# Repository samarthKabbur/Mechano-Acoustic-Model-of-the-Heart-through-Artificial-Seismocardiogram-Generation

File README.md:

# Mechano-Acoustic-Model-of-the-Heart-through-Artificial-Seismocardiogram-Generation

URF Project Development Proposal for a Mechano Acoustic Model of the Heart through Artificial Seismocardiogram Generation and Cardiac Tissue Modeling
PI: Dr. Nanshu Lu, Mentor: Sarnab Bhattacarya, Researcher: Samarth Kabbur, University of Texas at Austin
Background and Statement of Objectives
1 			2			3		

Figure 1: Assorted imagery. 1. Heart with muscle damage and blocked artery. 2. SCG data collection flowchart. 3. Proposed artificial seismocardiogram generation system.
“Intelligence will transform our ability to monitor and detect heart disease,” says Dr. Peter Libby, a renowned cardiologist at Harvard-affiliated Brigham and Women's Hospital.1 His words encapsulate the ever-increasing importance of leveraging cutting-edge technologies to address one of the most prevalent and impactful health concerns affecting the public today – cardiac complications (Fig 1.1). 
At the forefront of cardiac monitoring is seismocardiography, or SCG, which allows us to measure the mechanical motion of the heart. SCG has shown remarkable promise in its utility, holding the potential to revolutionize the early detection and prediction of atrial fibrillation6, CAD7, and heart failure6,7, potentially years before they manifest clinically (Fig 1.2). While the promise of SCG is undeniable, the development of sensors capable of accurately measuring SCG and deriving meaningful physical characteristics of the heart from its signals has been hindered by challenges. Progress has been slow, and the cost of development has been prohibitive.2 In response to these limitations I aim to create a device that advances upon the capabilities of existing artificial SCG waveform generators.This device will have the ability to artificially generate a wide range of waveforms, enabling researchers to rigorously test their SCG sensors by placing them on top of artificial tissue. By doing so, we will establish an anatomically accurate mechano-acoustic model of the heart, enabling the development and testing of non-invasive devices under various simulated heart conditions (Fig 1.3). The implications of such a device are profound, as it can be employed broadly in research clinics and commercial testing, provided it receives the necessary approvals.
While existing SCG Generator Phantoms have demonstrated the ability to replicate SCG waveforms with up to 90% accuracy, there remain several unexplored avenues.3 This research seeks to answer important questions regarding the use of alternative transduction methods, such as piezoelectric, for SCG generation. Additionally, by introducing configurable noise and artifact simulation into the system, this study aims to enhance the utility of artificial SCG signal generation for algorithm testing.
The significance of this study will be underscored if the developed device consistently and accurately reproduces SCG waveforms recorded by gold standard SCG sensors in real human subjects. Furthermore, the incorporation of artificial tissue layers into the waveform generation process holds the potential to contribute to the creation of more realistic SCG waveforms, advancing the state of the art in this field.This research is expected to be of particular interest to seismocardiogram researchers and those involved in SCG sensor development, as it promises to accelerate the testing phase of their projects. Many within our laboratory share these research interests.
In conclusion, the objectives of this study are twofold: the primary objective is to assess if the inclusion of artificial tissue composed of PDMS and other biopolymers enhances the accuracy of artificial SCG waveforms, while the secondary objective seeks to explore the procedural combination of noise artifacts with SCG waveforms.  It addresses critical questions, introduces innovative approaches, and holds the promise of improving the reliability and accuracy of SCG sensor technology.
Proposed Research Plan
    1			2	                  3			   4

Figure 2: Prototype results of a speaker based SCG transduction/generation platform. 1. The 10.7cm x 10.7cm base plate and ADXL355 accelerometer 2. The hexagonal cross-structure and sandwich. 3. Side profile reveals the Visaton EX60-S electrodynamic exciter, printed support base, bottom cushion, and the top placement of direct SCG measurement 4. rPi 3B computational structure for interface with the exciter and accelerometer. The rPi hat is developed by Nikbakht et.al.
2.1 Build and validate a speaker based SCG transduction platform that allows for the vibrational playback of Heartsound.wav waveforms.
Under the guidance of my mentor and previous work on a SCG Generator Phantom (hardware and software) by Nikbakht et.al3 I have developed a mechano-acoustic foundation for the artificial generation of SCG waveforms, a critical component of our research methodology (Fig 2). This system has been structured to facilitate validation through external sensor measurements. The core of this setup features a carefully designed base plate characterized by dimensions and curvature tailored to minimize internal echoes (Fig 2.1). Positioned atop this base plate is an accelerometer, responsible for recording the SCG waveform (Fig 2.1). To bolster mechanical coupling and optimize vibration transmission, a hexagonal cross structure is sandwiched within (Fig 2.2). The uppermost layer comprises a thin, rigid printed plastic roof plate, serving as the platform for the placement of the external SCG measurement device (Fig 2.3). Connecting these elements is a Raspberry Pi housing Python code that not only transmits the SCG waveform for playback but also collects internal vibration data from the accelerometer (Fig 2.4).
This endeavor benefits from the existence of more advanced software, as seen in the work by Nikbakht et.al. This software encompasses a comprehensive suite of features, including a feedback transfer function for waveform calibration against noise, error handling mechanisms, terminal-based inputs for precise control over playback, and it performs well on my mechanical model. In my research, I intend to draw inspiration from and further develop this existing codebase to refine and optimize my own system for SCG signal generation and validation.
	2.2 Build and study the effect of anatomically correct cardiac tissue layers composed of eco-polydimethylsiloxane and other bio-polymers on the generation of accurate artificial seismocardiogram waveforms.
SCG sensors do not sit directly on top of the heart, rather they read signals that need to travel through many layers of bone and tissue, including the myocardium, peritoneum, sternum, etc.2 Using our available eco-PDMS and other biopolymers as necessary, I will create layers of variable thickness, density, and composition to create a low-level structure mimicking the anatomical layers of the heart. The layers will rest on the top surface of the existing SCG Generator. Experimental testing will determine if the biostructure allows for a generation of a more accurate SCG signal, compared to a barebones platform. The testing will include varying the mechanical coupling between layers, changing the weight of the sensor itself, and varying tissue density all as independent variables.
	2.3 Create an algorithm that can incorporate noise artifacts (walking, running, stomach palpitations, small impulse) into a clean SCG signal.
Available SCG databases are limited, and sometimes a researcher may want to test their sensors on a unique signal that isn’t available to us. For example, the topic of research may deal with creating an e-tattoo that can detect SCG features while the patient is walking, running, etc. Citation no. 2 also describes this problem as a gap in existing literature. I will create a novel program that can combine noise artifacts generated by walking, running, hiking, swimming, etc. with a ‘clean’ SCG signal, in order to simulate a ‘dirty’ signal. Such a signal would then be played in the SCG Generator for testing purposes, allowing the researcher to test their device on a large variety of signals, all on a small in-house machine, allowing them to minimize expensive human trials.
Project Schedule and Milestones
Task
Subtask
Y1
Q1
Q2
Q3
Q4

1
Optimize and groove mechanical structure 

Mitigate external noise

2
Methodize variable density PDMS production

Manufacture tissue layers

Validate signal accuracy

3
Accumulate noisy and clean datasets

Procedural generation of noisy signal

Validate signal accuracy to ground truth

Review of Literature
A seminal external study that significantly informs the present research is the work titled "A Synthetic Seismocardiogram and Electrocardiogram Generator Phantom," authored by Mohammad Nikbakht et. al. This study introduced a portable and innovative system designed to synthetically generate SCG and electrocardiogram (ECG) signals. The researchers developed a Raspberry Pi-based system capable of replicating input SCG and ECG waveforms as physical acceleration and voltage outputs. For SCG generation, an off-the-shelf exciter speaker was employed as a mechanical transducer, and its transfer function was meticulously calibrated to ensure accurate replication of SCG waveforms. The system's performance was rigorously validated using human SCG and ECG data, achieving a remarkable >90% correlation between input and output signals in both time and frequency domains. Importantly, amplitude errors were maintained within clinically acceptable ranges, allowing the system to produce realistic waveforms with amplitudes corresponding to critical cardiac features. This innovation enables safe data collection in environments unsafe for human participants and provides a valuable source of ground truth signals.
While the aforementioned study represents a significant advancement in SCG signal generation, there remain opportunities for further development and improvement. First, expanding the validation process to encompass more diverse SCG morphologies, as well as various cardiac conditions, will enhance the applicability and reliability of the synthetic signal generator. The addition of noise artifacts associated with walking, running, and other forms of human mobility to the input waveform can help synthesize the effect of real world continuous processes on the heart. Finally, the proposed research seeks to build upon this foundation by creating a device that not only generates SCG signals but also incorporates artificial tissue layers to model the complex physiological nuances of the human body.
Budget
Raspberry Pi 4b+ KIT: Faster processor unlocks real time SCG processing and computationally intensive Python packages: $186
PDMS and Crosslinker: Biopolymer to simulate tissue layers: $175
Visaton 60s Electrodynamic Actuator x2: Generates the main SCG signal: $160
PAD Ex 60s x4: $120 x2: Adheres generator to surface, minimizes noise: $20
Piezoelectric Actuator: To study other methods of SCG generation: $12
Foam Padding: To pad external connections to minimize noise and internal vibration: $5
Polylactic Acid Filament: 3D printer material for foundation fabrication: $19
Ninjaflex Polyurethane Filament: 3D printer material for flexible plastics $28
Florida Biomedical Society 2024 Conference. (Coronado Springs, Florida, Feb 8-11, 8:30-10pm daily session time). The FBSS contains 48 hours of education sessions on topics relating to biomechanics. Researcher has identified these learning opportunities as valuable for the progress of his project, and has identified attending individuals, companies, and products highly relevant to this research and my career goals: $189 Registration Fee + $144 Hotel Fee. The researcher agrees to cover all extra conference related fees to guarantee attendance. (https://www.cmia.org/events/florida-biomedical-society-2024-symposium/)
Total: $938
The materials in the itemized budget are essential to the design and production of the proposal and validation study. While basic lab materials and electronic elements are available through courtesy of the PI, URF funding will expedite my research progress. It will also allow for stronger validation testing, robust manufacturing of the model, and quality materials.
References Cited
1.	Can a smart watch diagnose a heart attack? Harvard Health https://www.health.harvard.edu/heart-health/can-a-smart-watch-diagnose-a-heart-attack.
2.	Taebi, A., Solar, B. E., Bomar, A. J., Sandler, R. H. & Mansy, H. A. Recent Advances in Seismocardiography. Vibration 2, 64–86 (2019). doi: 10.3390/vibration2010005.
3.	A Synthetic Seismocardiogram and Electrocardiogram Generator Phantom. doi:10.1109/SENSORS52175.2022.9967101 
4.	Blocked Artery https://www.flickr.com/photos/nihgov/33328945325.
5.	Heart beat detection algorithm flowchart. https://www.researchgate.net/figure/Heart-beat-detection-algorithm-flowchart_fig3_33661771
6. M. Pankaala et al., “Detection of atrial fibrillation with seismocardiography,” doi: 10.1109/EMBC.2016.7591695.
7. I. Korzeniowska‐Kubacka, “Usefulness of Seismocardiography,” doi: 10.1111/j.1542-474X.2005.00547.x.

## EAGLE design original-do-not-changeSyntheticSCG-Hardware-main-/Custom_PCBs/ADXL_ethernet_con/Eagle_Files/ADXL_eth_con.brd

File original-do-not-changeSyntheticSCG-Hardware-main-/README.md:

# Synthetic ECG SCG Generator Hardware

The seismocardiogram (SCG) is a measure of chest wall vibrations resulting from the heartbeat. The SCG is typically
recorded using a low-noise accelerometer placed on the mid-sternum and contains features related to cardiovascular
activity such as aortic valve opening (AO) and aortic closing (AC). These features can support assessment of cardiovascular health and have been used in conjunction with other physiological signals to monitor key health parameters such as blood volume status and intracardiac filling pressures.

Electrocardiogram (ECG) signal reflects the electrical activity of the heart observed from the strategic points of the human body and represented by quasi-periodic voltage signal.
<!-- 
These signals fiducial points correspond to characteristic events in the cardiac cycle. For the SCG, the labels correspond to the physiological event they are believed to represent: MC, mitral valve closure; IVC, isovolumetric contraction; AO, aortic valve opening; RE, rapid ejection; AC, aortic valve closure; MO, mitral valve open- ing; and RF, rapid filling. -->

<!-- However, SCG signals are small signal, and they can get distorted easily by motion artifacts. Therefore exploring denoising methods is of great importance for SCG signals. Clearing out the noise enables extraction of physiologically relevant information from SCG. To study denoising methods, we need to collect SCG signals in noisy environments, but it is unsafe to use human subjects for such data collection in some high motion environments (medical transport helicopters). To address this, here we designed a phantom that can generate SCG and ECG signals synthetically. This enables us to collect data in those noisy environmnets without human subject involvement.
 -->
In this work, we introduce a portable USB-C powered Raspberry Pi-based system that can replicate any SCG and ECG signal inputs with minimal error in forms of acceleration and voltage. The SCG signals are generated using an off the shelf exciter speaker, and the ECG signals are generated using a voltage amplifier through 3 conductive pads. The generated signals can be recorded using the same wearable devices that are used to measure human SCG and ECG signals. Thus, this system can be used as a safer, more convenient alternative to human participants in high external vibration environments for testing and validating
classification/regression tasks and noise reduction algorithms.

## The Hardware 

he system proposed in this work consists of an actuator unit and a processing unit. The actuator unit, which generates SCG and ECG signals. 

<!--  -->

The system designed here offers two user-controlled modes of operation: (1) calibration, which re-estimates the transfer function of the exciter speaker with the added load on the platform (wearable sensors) , and (2) signal generation, which generates the ECG and SCG sequences.

A block diagram of the system operation:

### Commands

1) Calibration mode: Calibrate the system (in a new environment):

calculate the transfer function of the actuator using a sine sweep and use it to calibrate the SCG beats to be ready for generation
 
```console
python3 SCG_Generator.py tf_estimate desktop
python3 SCG_Generator.py calibrate seq_synth desktop (or any file name [without .pkl])
```
<!-- 
 -->

2) Generation mode: Generate SCG waveforms:

generate SCG and ECG signals using the calibrated beats stored in the previous step

```console
python3 SCG_Generator.py generate seq_synth_calibrated desktop (or any file name you stored the calibrated signals [without .pkl])
```

<!--  -->

## Use

Depending on the type of the connection to the RPi, there are 2 options:
1) If a display is connected to the RPi (or have X11 forwarding enabled), the plots will be shown in separate windows. Use this command (this mode is default):
```console
python3 SCG_generate.py generate signal_sample_calibrated desktop
```
2) If communication is through a terminal only, the plots will be plotted in the terminal (lower quality). Use this command:
```console
python3 SCG_generate.py generate signal_sample_calibrated terminal
```
## Output Recording Samples

A sample of the generator-output SCG and ECG compared to the ECG and SCG inputs:

Bland-Altman plots of error between the measured generator-output and the real human signal input based on the amplitude of the most prominent
feature of the beats after heartbeat segmentation for (a) SCG, and (b) ECG signals. 

<!-- Zoomed in:

 -->

## Reference

Please cite this paper:

M. Nikbakht, D. J. Lin, A. H. Gazi, and O. T. Inan, “A synthetic
seismocardiogram and electrocardiogram generator phantom,” in 2022
IEEE Sensors, in press.

BibTeX format: 

@inproceedings{nikbakht2022synthetic,
title={A Synthetic Seismocardiogram and Electrocardiogram Generator Phantom},
author={Nikbakht, Mohammad, and Lin, David J., and Gazi, Asim H., and Inan, Omer T.},
note={in press},
booktitle={2022 IEEE Sensors},
% pages={Accepted},
% year={2022},
% organization={IEEE}
}

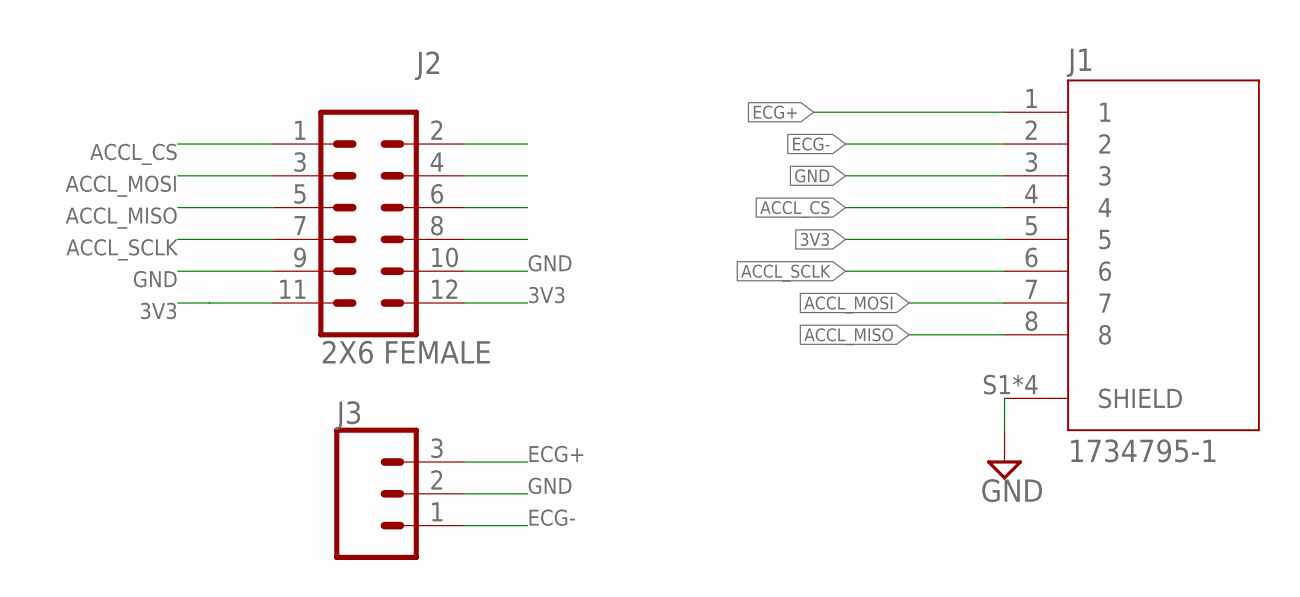
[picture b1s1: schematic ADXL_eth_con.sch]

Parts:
J1: 1734795-1; TE_1734795-1
J2: 2X6 FEMALE; 2X6
J3: CONN_03; 1X03

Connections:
3V3: J1.5, J2.11, J2.12
ACCL_CS: J1.4, J2.1
ACCL_MISO: J1.8, J2.5
ACCL_MOSI: J1.7, J2.3
ACCL_SCLK: J1.6, J2.7
ECG+: J1.1, J3.3
ECG-: J1.2, J3.1
GND: J1.3, J1.S1 (SHIELD), J1.S2 (SHIELD), J1.S3 (SHIELD), J1.S4 (SHIELD), J2.9, J2.10, J3.2

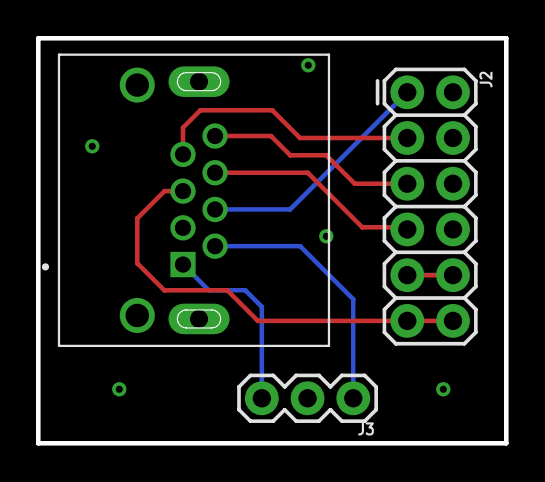
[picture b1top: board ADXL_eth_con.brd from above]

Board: 2 copper layers, 26.0 x 22.5 mm, 3 parts (0 on the bottom side), 8 nets.

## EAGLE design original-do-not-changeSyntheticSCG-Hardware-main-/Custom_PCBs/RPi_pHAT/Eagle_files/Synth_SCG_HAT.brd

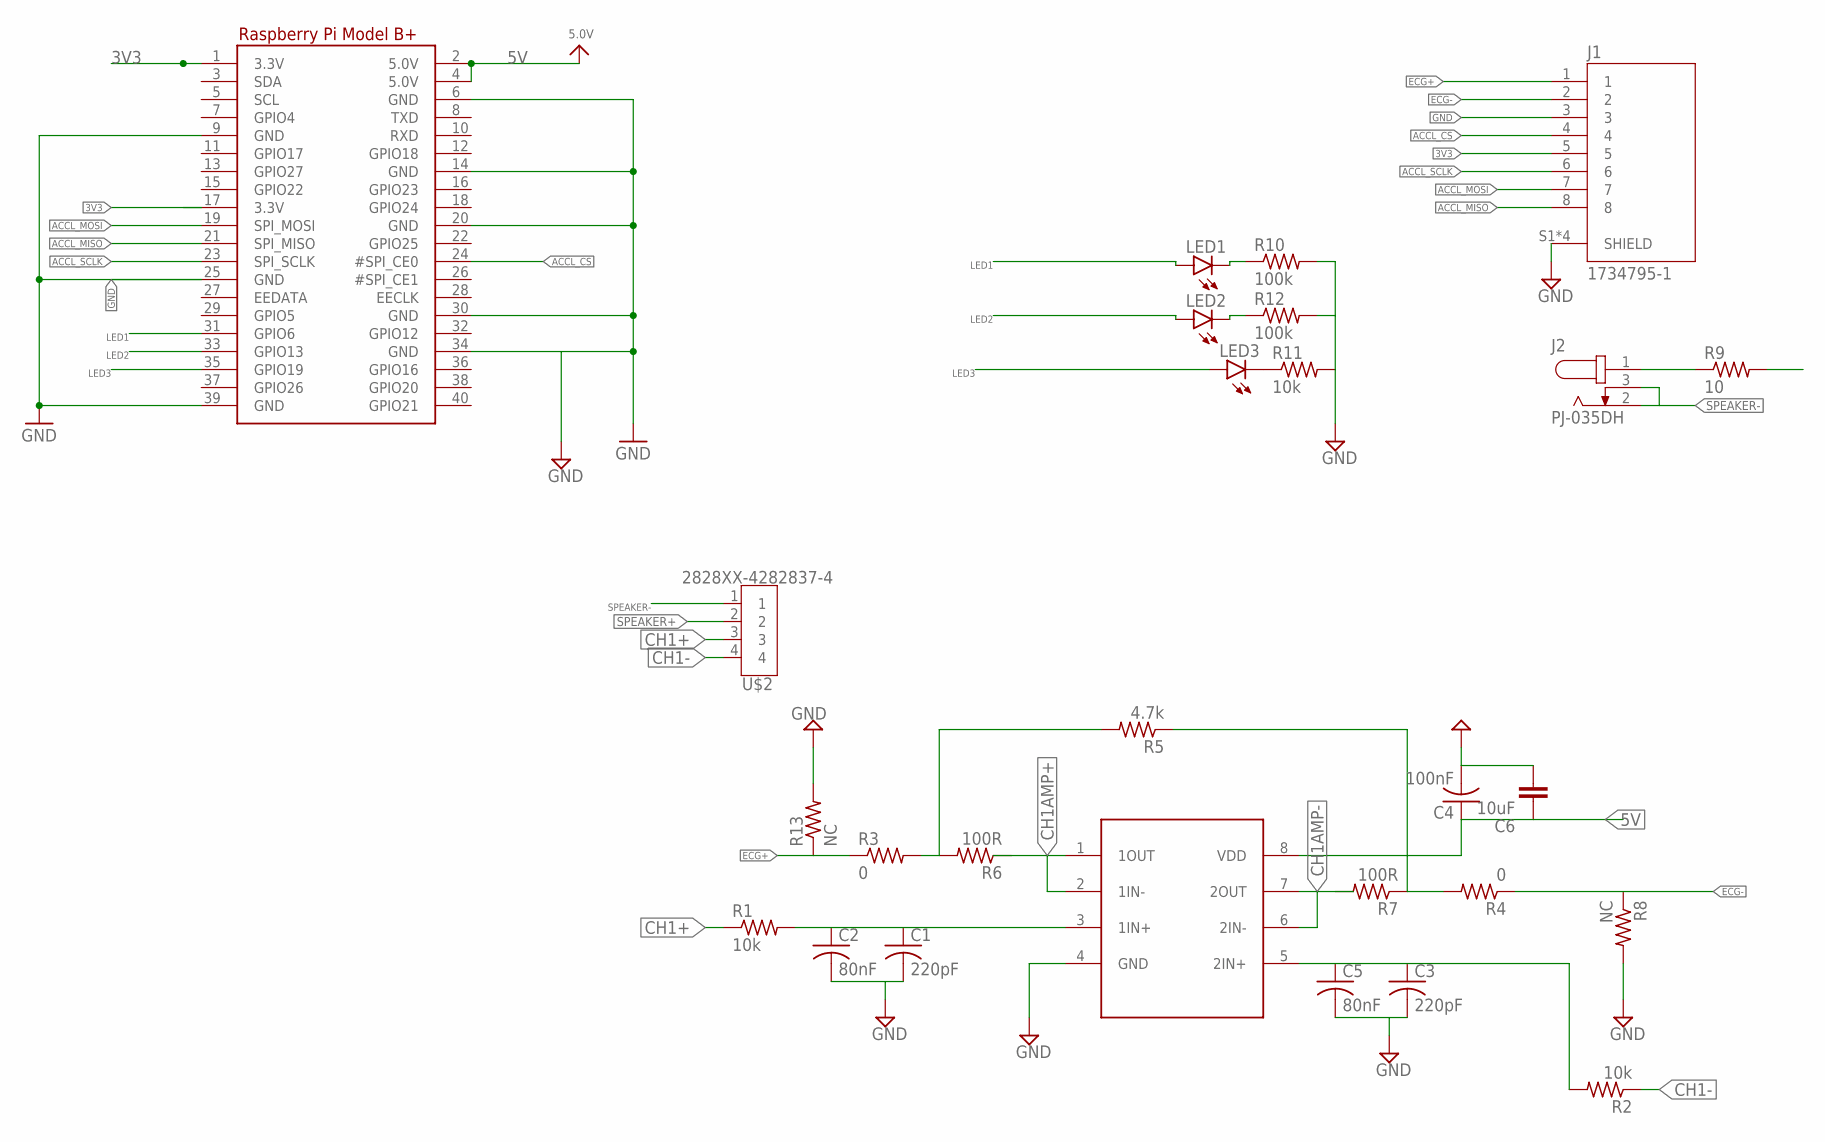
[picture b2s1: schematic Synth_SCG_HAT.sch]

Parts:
C1, C3: 220pF; CAPC3216X135
C2, C5: 80nF; CAPC2012X110
C4: 100nF; CAPC1608X85
C6: 10uF; CAPM3216X180
J1: 1734795-1; TE_1734795-1
J2: PJ-035DH; CUI_PJ-035DH
LED1, LED2, LED3: LEDCHIPLED_1206; CHIPLED_1206
R1, R2, R11: 10k; R0603
R3, R4: 0; R0603
R5: 4.7k; R0603
R6, R7: 100R; R0603
R8, R13: NC; R0603
R9: 10; R0603
R10, R12: 100k; R0603
RPI1: RASPBERRYPI_BPLUS_BONNETNODIM; PI_BONNET_NODIM
U$1: TLV4112; DIP794W45P254L959H508Q8
U$2: 2828XX-4282837-4; TERMBLK_508-4N

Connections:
3.3V@1: RPI1.17 (3.3V)
3V3: J1.5, RPI1.1 (3.3V)
5V: C4.1, C6.1, RPI1.2 (5.0V), RPI1.4 (5.0V), U$1.8 (VDD)
ACCL_CS: J1.4, RPI1.24 (#SPI_CE0)
ACCL_MISO: J1.8, RPI1.21 (SPI_MISO)
ACCL_MOSI: J1.7, RPI1.19 (SPI_MOSI)
ACCL_SCLK: J1.6, RPI1.23 (SPI_SCLK)
CH1+: R1.1, U$2.3
CH1-: R2.1, U$2.4
CH1AMP+: R6.1, U$1.1 (1OUT), U$1.2 (1IN-)
CH1AMP-: R7.2, U$1.6 (2IN-), U$1.7 (2OUT)
ECG+: J1.1, R3.1, R13.1
ECG-: J1.2, R4.1, R8.1
GND: C1.2, C2.2, C3.2, C4.2, C5.2, C6.2, J1.3, J1.S1 (SHIELD), J1.S2 (SHIELD), J1.S3 (SHIELD), J1.S4 (SHIELD), R8.2, R10.2, R11.2, R12.2, R13.2, RPI1.6 (GND), RPI1.9 (GND), RPI1.14 (GND), RPI1.20 (GND), RPI1.25 (GND), RPI1.30 (GND), RPI1.34 (GND), RPI1.39 (GND), U$1.4 (GND)
LED1: LED1.A, RPI1.31 (GPIO6)
LED2: LED2.A, RPI1.33 (GPIO13)
LED3: LED3.A, RPI1.35 (GPIO19)
unnamed: C1.1, C2.1, R1.2, U$1.3 (1IN+)
unnamed: R3.2, R5.2, R6.2
unnamed: C3.1, C5.1, R2.2, U$1.5 (2IN+)
unnamed: J2.1, R9.1
unnamed: R4.2, R5.1, R7.1
unnamed: LED3.C, R11.1
unnamed: LED2.C, R12.1
unnamed: LED1.C, R10.1
SPEAKER+: R9.2, U$2.2
SPEAKER-: J2.2, J2.3, U$2.1

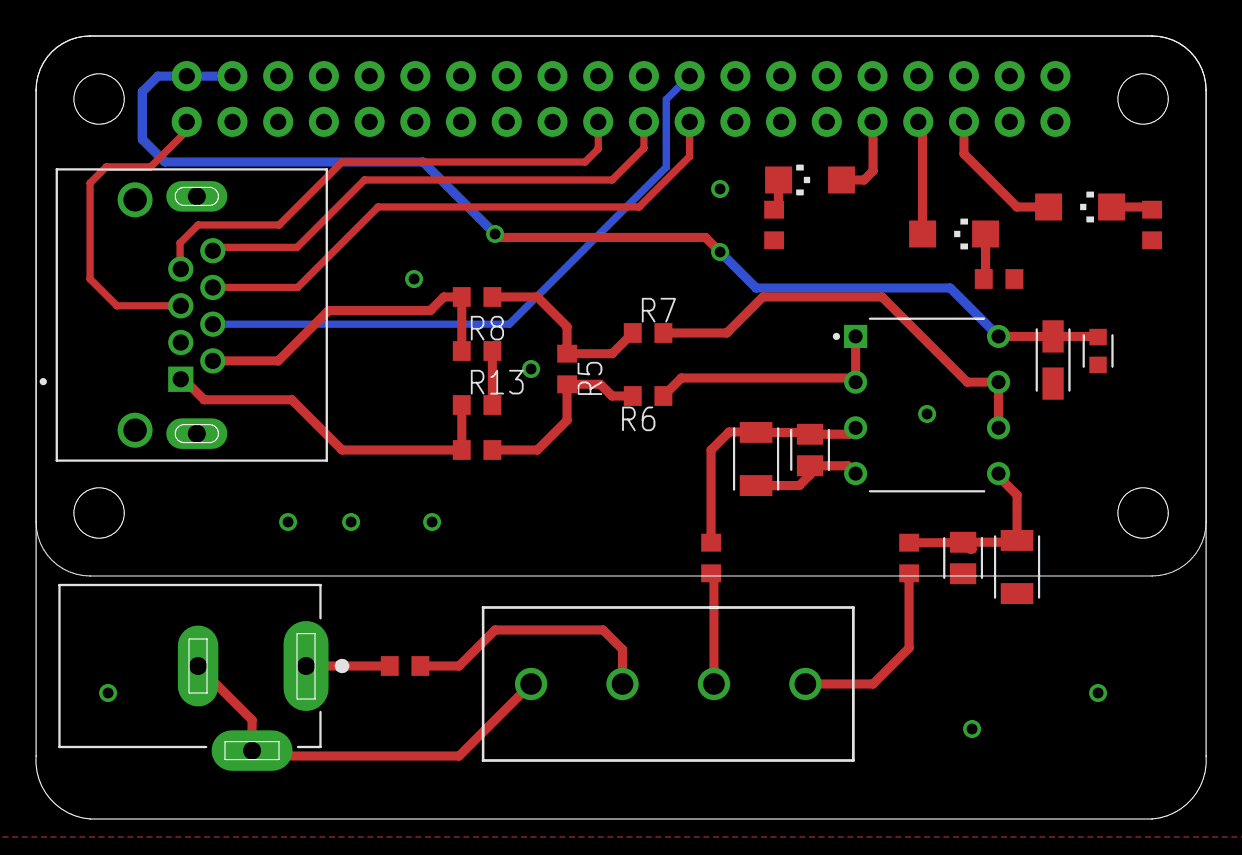
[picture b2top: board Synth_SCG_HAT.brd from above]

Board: 2 copper layers, 65.0 x 43.5 mm, 27 parts (0 on the bottom side), 26 nets.

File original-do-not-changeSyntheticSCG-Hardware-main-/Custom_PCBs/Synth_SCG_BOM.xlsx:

Part | Value | Device | Package | DigiKey Part Number
C1 | 220pF | C-US_CHIP-1206(3216-METRIC) | CAPC3216X135
C2 | 80nF | C-US_CHIP-0805(2012-METRIC) | CAPC2012X110
C3 | 220pF | C-US_CHIP-1206(3216-METRIC) | CAPC3216X135
C4 | 100nF | C-US_CHIP-0603(1608-METRIC) | CAPC1608X85
C5 | 80nF | C-US_CHIP-0805(2012-METRIC) | CAPC2012X110
C6 | 10uF | C_TANTALUM-1206(3216-METRIC) | CAPM3216X180
J1 | 1734795-1 | 1734795-1 | TE_1734795-1 | A121573-ND
J2 | PJ-035DH | PJ-035DH | CUI_PJ-035DH | CP-017DH-ND
LED1 |  | LEDCHIPLED_1206 | CHIPLED_1206
LED2 |  | LEDCHIPLED_1206 | CHIPLED_1206
LED3 |  | LEDCHIPLED_1206 | CHIPLED_1206
R1 | 10k | R-US_R0603 | R0603
R2 | 10k | R-US_R0603 | R0603
R3 | 0 | R-US_R0603 | R0603
R4 | 0 | R-US_R0603 | R0603
R5 | 4.7k | R-US_R0603 | R0603
R6 | 100R | R-US_R0603 | R0603
R7 | 100R | R-US_R0603 | R0603
R8 | NC | R-US_R0603 | R0603
R9 | 10 | R-US_R0603 | R0603
R10 | 100k | R-US_R0603 | R0603
R11 | 10k | R-US_R0603 | R0603
R12 | 100k | R-US_R0603 | R0603
R13 | NC | R-US_R0603 | R0603
RPI1 | RASPBERRYPI_BPLUS_BONNETNODIM | I2S 3W STEREO SPEAKER AMP BONNET | I2S 3W STEREO SPEAKER AMP BONNET | 1528-1819-ND
U$1 | TLV4112 | TLV4112 | DIP794W45P254L959H508Q8 | 296-10719-5-ND
U$2 | 2828XX-4282837-4 | 2828XX-4282837-4 | TERMBLK_508-4N | 281-1437-ND
 | Extra parts (digikey): |  | count
 | 2x20 Socket Riser Header for Rpi | 1528-2831-ND | 2
 | RPI female header | 1528-1785-ND | 2
 | RPi connector | 1568-1675-ND | 2
 | RPi stacking header | 1528-1385-ND
 | 12 Position Header Connector 0.100" (2.54mm) Through Hole, Right Angle | S5559-ND | 2
 | DC plug 3.5 | EP505B-ND | 2
 | Terminal blocks | ED2611-ND | 2
 | Terminal blocks | A97986-ND | 2
 | Dip socket | ED3044-5-ND | 2
 | Raspberry Pi 4 8GB | 2648-RASPBERRYPI4MODELB8G-ND | 1
 | ADXL355 eval board | 505-EVAL-ADXL355-PMDZ-ND | 1
 | ECG electrode pads | 1568-1803-ND | 2
 | Visaton EX 60 S Exciter Speaker | 2056-EX60S-8OHM-ND
 | screw and bolt 4mm
 | super glue + electric tape
 | Extra parts (Amazon):
 | Ethernet cable | https://www.amazon.com/Ethernet-Cable-1000Mbps-Universal-Com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
 | micro-SD card 32GB or 64GB

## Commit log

2023-10-31 unchanged RPi code + old code and waves
2023-10-31 updated directories
2023-11-01 new tf, calibration, generation on oldbase
2023-11-01 Update README.md to include URF proposal and grant
2023-11-01 tested old and new base. added plots
2024-02-12 adding scg generator folder
2024-02-12 added SCG generator folder
    contains adxl 355 to ethernet info, custon scg housing solidworks files, adxl 355 pinout info, phonocardiogram playback under procedural scg generation, rpi sd card backup, mohammad's OG code, and ti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

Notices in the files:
parts and their libraries:
SparkFun-Connectors: Licensing: Creative Commons ShareAlike 4.0 International - https://creativecommons.org/licenses/by-sa/4.0
microbuilder: This work is placed in the public domain, and may be freely used for commercial and non-commercial work with the following conditions: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
